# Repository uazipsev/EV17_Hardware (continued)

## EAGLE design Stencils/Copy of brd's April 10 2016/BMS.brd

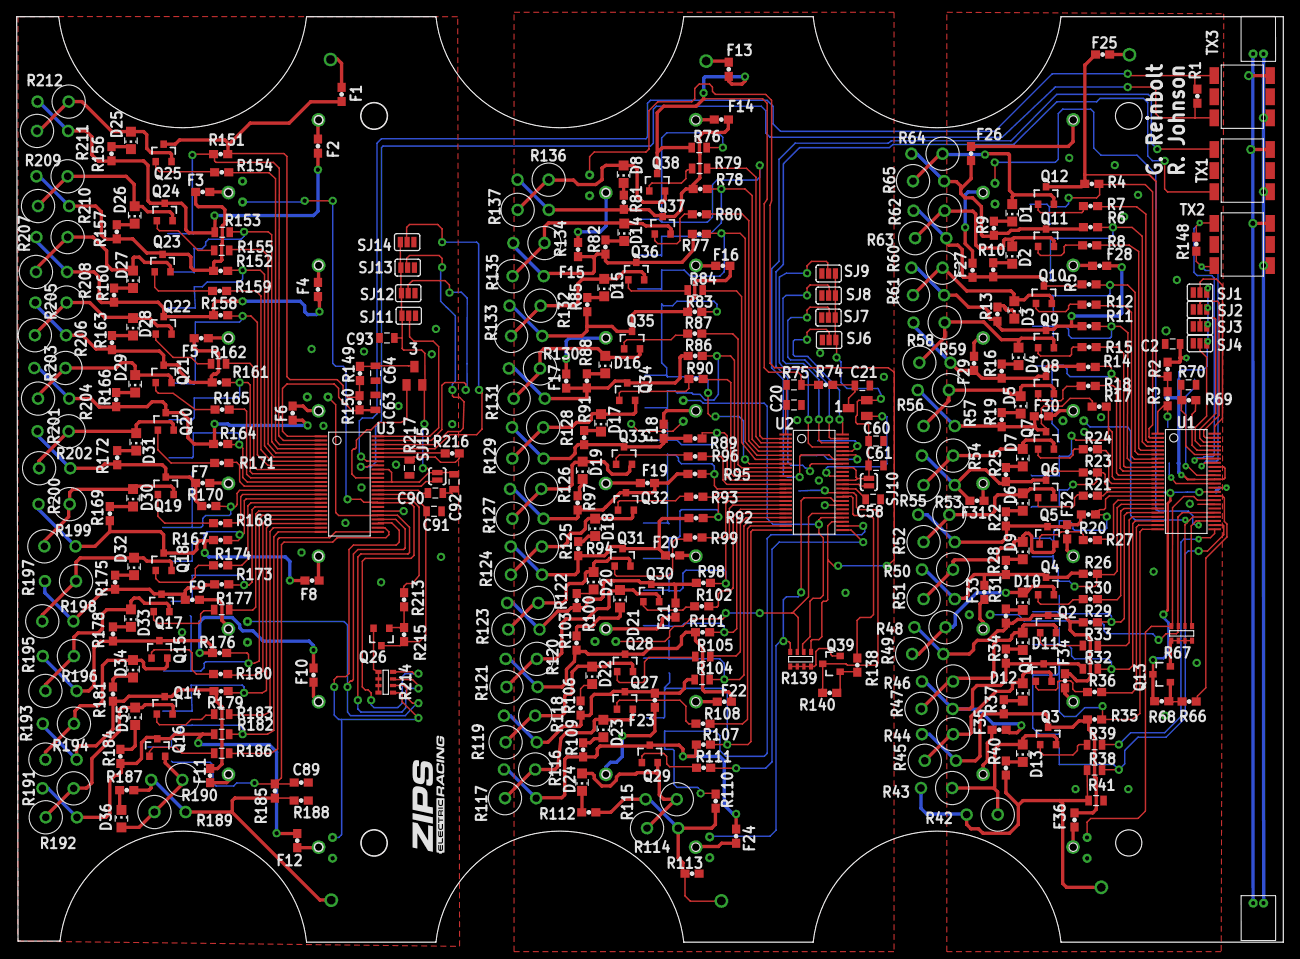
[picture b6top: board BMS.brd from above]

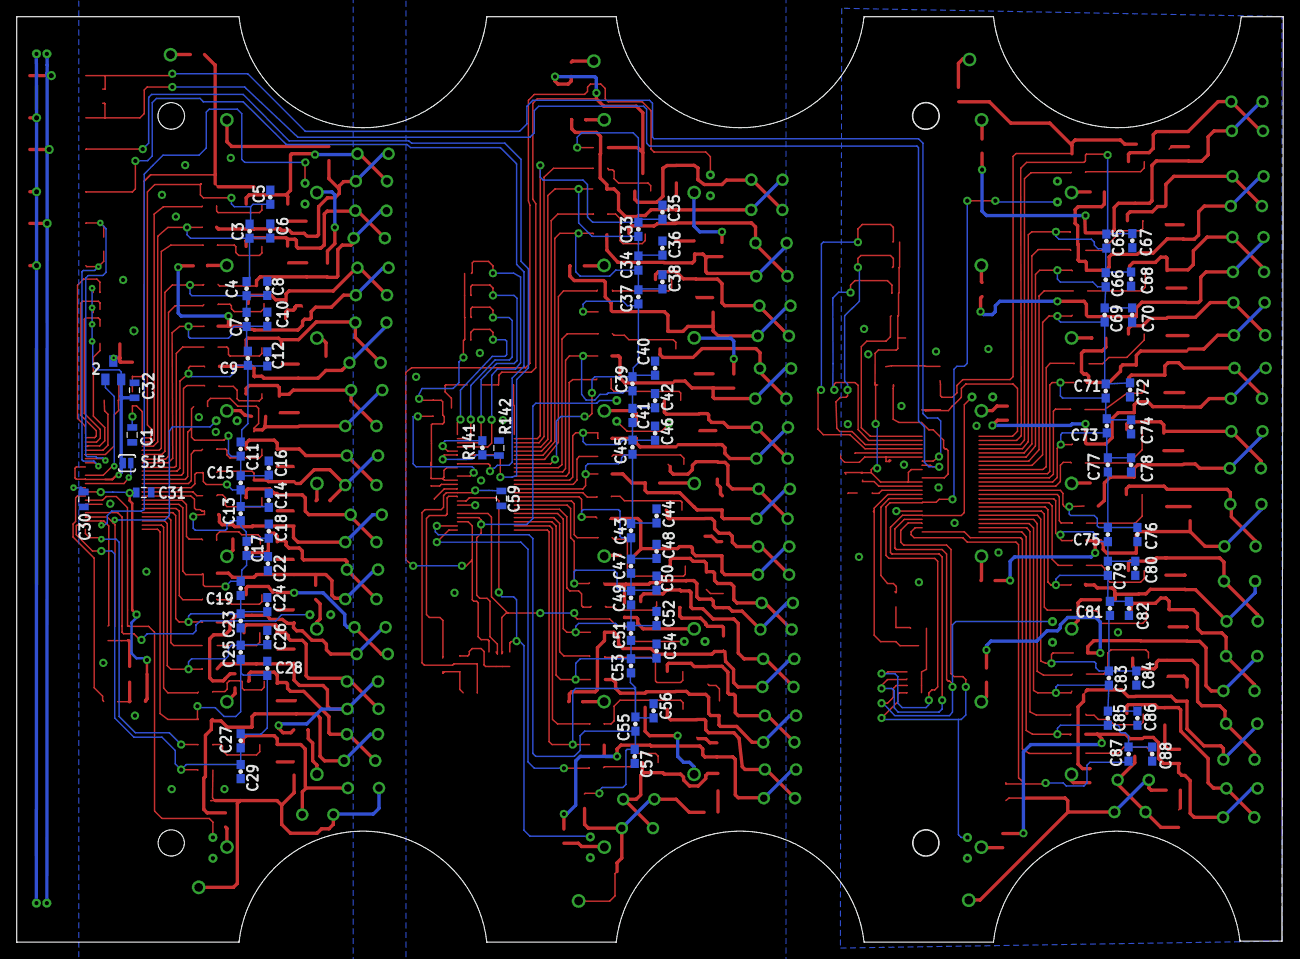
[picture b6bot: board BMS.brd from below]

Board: 2 copper layers, 152.4 x 111.4 mm, 490 parts (83 on the bottom side), 329 nets.

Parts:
1, 2, 3: BCV71SMD; SOT23-BEC
C1, C2, C20, C21, C63, C64: 0.1UF; 0805
C3, C4, C7, C9, C11, C13, C15, C17, C19, C23, C25, C27, C29, C33, C34, C37, C39, C41, C43, C45, C47, C49, C51, C53, C55, C57, C65, C66, C69, C71, C73, C75, C77, C79, C81, C83, C85, C87, C89: 10NF; 0603
C5, C6, C8, C10, C12, C14, C16, C18, C22, C24, C26, C28, C35, C36, C38, C40, C42, C44, C46, C48, C50, C52, C54, C56, C67, C68, C70, C72, C74, C76, C78, C80, C82, C84, C86, C88: DNP; 0603
C30, C31, C32, C58, C59, C60, C61, C90, C91, C92, C93: 1UF; 0805
D1, D2, D3, D4, D5, D6, D7, D8, D9, D10, D11, D12, D13, D14, D15, D16, D17, D18, D19, D20, D21, D22, D23, D24, D25, D26, D27, D28, D29, D30, D31, D32, D33, D34, D35, D36: LED_RED; CHIP_LED0805
F1, F2, F3, F4, F5, F6, F7, F8, F9, F10, F11, F12, F13, F14, F15, F16, F17, F18, F19, F20, F21, F22, F23, F24, F25, F26, F27, F28, F29, F30, F31, F32, F33, F34, F35, F36: FUSE_750MA_63V_0603; 0603
J1, J2: M2_DF13-2P; DF13-2P
Q1, Q2, Q3, Q4, Q5, Q6, Q7, Q8, Q9, Q10, Q11, Q12, Q13, Q14, Q15, Q16, Q17, Q18, Q19, Q20, Q21, Q22, Q23, Q24, Q25, Q26, Q27, Q28, Q29, Q30, Q31, Q32, Q33, Q34, Q35, Q36, Q37, Q38, Q39: BSS308PE; SOT23
R1, R148: DNP; 0603
R2, R3, R4, R5, R6, R11, R14, R17, R20, R23, R26, R29, R35, R74, R77, R78, R83, R86, R89, R92, R95, R98, R101, R107, R110, R149, R150, R151, R152, R158, R161, R164, R167, R170, R173, R176, R179, R185: 100; 0603
R7, R8, R12, R15, R18, R21, R24, R27, R30, R36, R80, R87, R90, R93, R96, R99, R102, R108, R111, R154, R159, R165, R168, R171, R174, R180: 3.3K; 0603
R9, R10, R13, R16, R19, R22, R25, R28, R31, R34, R37, R40, R81, R82, R85, R88, R91, R94, R97, R100, R103, R106, R109, R112, R156, R157, R160, R163, R166, R169, R172, R175, R178, R181, R184, R187: 475; 0603
R32, R38, R75, R76, R104, R153, R182: 100; 0805
R33, R39, R79, R84, R105, R155, R162, R177, R183, R186: 3.3K; 0805
R41: 0; 0805
R42, R43, R44, R45, R46, R47, R48, R49, R50, R51, R52, R53, R54, R55, R56, R57, R58, R59, R60, R61, R62, R63, R64, R65, R114, R115, R116, R117, R118, R119, R120, R121, R122, R123, R124, R125, R126, R127, R128, R129, R130, R131, R132, R133, R134, R135, R136, R137, R189, R190, R191, R192, R193, R194, R195, R196, R197, R198, R199, R200, R201, R202, R203, R204, R205, R206, R207, R208, R209, R210, R211, R212: 16; RR02J16RTB
R66, R138, R213: 1K; 0603
R67, R139, R214: 10K; MNR14
R68, R140, R215: 100K; 0603
R69, R141, R216: 1.2K; 0603
R70, R142, R217: 787; 0805
R71, R72, R73, R143, R144, R145, R146, R147, R218, R219, R220, R221: 10K-NTC; NTC-NXRT15XH103FA5B
R113, R188: 0; 0603
SJ1, SJ2, SJ3, SJ4, SJ6, SJ7, SJ8, SJ9, SJ11, SJ12, SJ13, SJ14: PAD-JUMPER-3-NO_YES_SILK
SJ5, SJ10, SJ15: PAD-JUMPER-2-NO_YES_SILK
TX1, TX2, TX3: PE-68386NLT
U1, U2, U3: LTC6804-2; SSOP-48
U$1, U$2, U$3, U$4, U$5, U$6, U$7, U$8, U$9, U$10, U$11, U$12, U$13, U$14, U$15, U$16, U$17, U$18, U$19, U$20, U$21, U$22, U$23, U$24, U$25, U$26, U$40, U$41, U$42, U$43, U$44, U$45, U$46, U$47, U$48, U$49, U$50, U$51, U$52: POGOPIN
U$27: LOGO16-2-L; 2016-2-LOGO-L

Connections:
A0: SJ9.2, U2.45
A1: SJ8.2, U2.46
A2: SJ7.2, U2.47
A3: SJ6.2, U2.48
A4: SJ4.2, U1.45
A5: SJ3.2, U1.46
A6: SJ2.2, U1.47
A7: SJ1.2, U1.48
A8: SJ14.2, U3.45
A9: SJ13.2, U3.46
A10: SJ12.2, U3.47
A11: SJ11.2, U3.48
C0: C55.2, C57.1, R110.2, U2.26
C1: C53.2, C55.1, C56.1, R107.2, U2.24
C2: C51.2, C53.1, C54.1, R104.2, U2.22
C3: C49.2, C51.1, C52.1, R101.2, U2.20
C4: C47.2, C49.1, C50.1, R98.2, U2.18
C5: C43.2, C47.1, C48.1, R92.2, U2.16
C6: C43.1, C44.1, C45.2, R95.2, U2.14
C7: C41.2, C45.1, C46.1, R89.2, U2.12
C8: C39.2, C41.1, C42.1, R86.2, U2.10
C9: C37.2, C39.1, C40.1, R83.2, U2.8
C10: C34.2, C37.1, C38.1, R77.2, U2.6
C11: C33.2, C34.1, C36.1, R78.2, U2.4
C12: C33.1, C35.1, R76.2, U2.2
C13: C3.1, C5.1, R4.2, U1.2
C14: C3.2, C4.1, C6.1, R6.2, U1.4
C15: C7.2, C9.1, C10.1, R11.2, U1.8
C16: C11.2, C15.1, C16.1, R17.2, U1.12
C17: C13.1, C14.1, C15.2, R23.2, U1.14
C18: C13.2, C17.1, C18.1, R20.2, U1.16
C19: C19.2, C23.1, C24.1, R29.2, U1.20
C20: C23.2, C25.1, C26.1, R32.2, U1.22
C21: C25.2, C27.1, C28.1, R35.2, U1.24
C22: C4.2, C7.1, C8.1, R5.2, U1.6
C23: C27.2, C29.1, R38.2, U1.26
C24: C17.2, C19.1, C22.1, R26.2, U1.18
C25: C9.2, C11.1, C12.1, R14.2, U1.10
C26: C65.1, C67.1, R151.2, U3.2
C27: C65.2, C66.1, C68.1, R153.2, U3.4
C28: C69.2, C71.1, C72.1, R158.2, U3.8
C29: C73.2, C77.1, C78.1, R164.2, U3.12
C30: C75.1, C76.1, C77.2, R170.2, U3.14
C31: C75.2, C79.1, C80.1, R167.2, U3.16
C32: C81.2, C83.1, C84.1, R176.2, U3.20
C33: C83.2, C85.1, C86.1, R179.2, U3.22
C34: C85.2, C87.1, C88.1, R182.2, U3.24
C35: C66.2, C69.1, C70.1, R152.2, U3.6
C36: C87.2, C89.1, R185.2, U3.26
C37: C79.2, C81.1, C82.1, R173.2, U3.18
C38: C71.2, C73.1, C74.1, R161.2, U3.10
DRIVE: 1.B, U2.38
DRIVE1: 2.B, U1.38
DRIVE2: 3.B, U3.38
GND: C63.2, C64.2, C67.2, C68.2, C70.2, C72.2, C74.2, C76.2, C78.2, C80.2, C82.2, C84.2, C86.2, C88.2, C89.2, C90.2, C91.2, C92.2, C93.2, R188.2, R217.1, R218.P$1, R219.P$1, R220.P$1, R221.P$1, SJ11.3, SJ12.3, SJ13.3, SJ14.3, U3.30, U3.31
GNDA: C20.2, C21.2, C35.2, C36.2, C38.2, C40.2, C42.2, C44.2, C46.2, C48.2, C50.2, C52.2, C54.2, C56.2, C57.2, C58.2, C59.2, C60.2, C61.2, R113.2, R142.1, R143.P$1, R144.P$1, R145.P$1, R146.P$1, SJ6.3, SJ7.3, SJ8.3, SJ9.3, U2.30, U2.31
GNDI: C1.2, C2.2, C5.2, C6.2, C8.2, C10.2, C12.2, C14.2, C16.2, C18.2, C22.2, C24.2, C26.2, C28.2, C29.2, C30.2, C31.2, C32.2, R41.2, R70.1, R71.P$1, R72.P$1, R73.P$1, R147.P$1, SJ1.3, SJ2.3, SJ3.3, SJ4.3, U1.30, U1.31
GPIO1: R139.1, R143.P$2, U2.27
GPIO2: R139.2, R144.P$2, U2.28
GPIO3: R139.3, R145.P$2, U2.29
GPIO4: R139.4, R146.P$2, U2.32
GPIO5: R138.2, U2.33
GPIO6: R67.2, R72.P$2, U1.28
GPIO7: R67.1, R71.P$2, U1.27
GPIO8: R67.4, R147.P$2, U1.32
GPIO9: R67.3, R73.P$2, U1.29
GPIO10: R66.2, U1.33
GPIO11: R214.2, R219.P$2, U3.28
GPIO12: R214.1, R218.P$2, U3.27
GPIO13: R214.4, R221.P$2, U3.32
GPIO14: R214.3, R220.P$2, U3.29
GPIO15: R213.2, U3.33
IBIAS: R141.2, U2.44
IBIAS1: R69.2, U1.44
IBIAS2: R216.2, U3.44
ICMP: R141.1, R142.2, U2.43
ICMP1: R69.1, R70.2, U1.43
ICMP2: R216.1, R217.2, U3.43
IMA: TX1.3, U2.41
IMA1: R148.2, TX2.3, U1.41
IMA2: R1.2, TX3.3, U3.41
IPA: TX1.1, U2.42
IPA1: R148.1, TX2.1, U1.42
IPA2: R1.1, TX3.1, U3.42
unnamed: Q12.1, R7.1
unnamed: D1.A, Q12.2, R64.P$2, R65.P$2
unnamed: D1.C, R9.2
unnamed: F26.2, Q11.3, R6.1, R9.1, R64.P$1, R65.P$1
unnamed: Q11.1, R8.1
unnamed: D2.A, Q11.2, R62.P$2, R63.P$2
unnamed: D2.C, R10.2
unnamed: F27.2, Q10.3, R5.1, R10.1, R62.P$1, R63.P$1
unnamed: Q10.1, R12.1
unnamed: D3.A, Q10.2, R60.P$2, R61.P$2
unnamed: D3.C, R13.2
unnamed: F28.2, Q9.3, R11.1, R13.1, R60.P$1, R61.P$1
unnamed: Q9.1, R15.1
unnamed: D4.A, Q9.2, R58.P$2, R59.P$2
unnamed: D4.C, R16.2
unnamed: F29.2, Q8.3, R14.1, R16.1, R58.P$1, R59.P$1
unnamed: Q8.1, R18.1
unnamed: D5.A, Q8.2, R56.P$2, R57.P$2
unnamed: D5.C, R19.2
unnamed: Q6.1, R21.1
unnamed: D6.A, Q6.2, R52.P$2, R53.P$2
unnamed: D6.C, R22.2
unnamed: F30.2, Q7.3, R17.1, R19.1, R56.P$1, R57.P$1
unnamed: Q7.1, R24.1
unnamed: D7.A, Q7.2, R54.P$2, R55.P$2
unnamed: D7.C, R25.2
unnamed: F31.2, Q6.3, R23.1, R25.1, R54.P$1, R55.P$1
unnamed: F32.2, Q5.3, R20.1, R22.1, R52.P$1, R53.P$1
unnamed: Q5.1, R27.1
unnamed: D9.A, Q5.2, R50.P$2, R51.P$2
unnamed: D9.C, R28.2
unnamed: F33.2, Q4.3, R26.1, R28.1, R50.P$1, R51.P$1
unnamed: Q4.1, R30.1
unnamed: D10.A, Q4.2, R48.P$2, R49.P$2
unnamed: D10.C, R31.2
unnamed: F34.2, Q2.3, R29.1, R31.1, R48.P$1, R49.P$1
unnamed: Q2.1, R33.1
unnamed: D11.A, Q2.2, R46.P$2, R47.P$2
unnamed: D11.C, R34.2
unnamed: F35.2, Q1.3, R32.1, R34.1, R46.P$1, R47.P$1
unnamed: Q1.1, R36.1
unnamed: D12.A, Q1.2, R44.P$2, R45.P$2
unnamed: D12.C, R37.2
unnamed: Q3.1, R39.1
unnamed: D13.C, R40.2
unnamed: F25.2, Q12.3, R2.1, R3.1, R4.1
unnamed: D13.A, Q3.2, R42.P$2, R43.P$2
unnamed: R38.1, R40.1, R41.1, R42.P$1, R43.P$1, U$1.1
unnamed: F36.2, Q3.3, R35.1, R37.1, R44.P$1, R45.P$1
unnamed: 2.C, C2.1, R2.2
unnamed: Q13.2, R67.5, R67.6, R67.7, R67.8
unnamed: Q13.1, R66.1, R68.1
unnamed: Q25.1, R154.1
unnamed: D25.A, Q25.2, R211.P$2, R212.P$2
unnamed: D25.C, R156.2
unnamed: F2.2, Q24.3, R153.1, R156.1, R211.P$1, R212.P$1
unnamed: Q24.1, R155.1
unnamed: D26.A, Q24.2, R209.P$2, R210.P$2
unnamed: D26.C, R157.2
unnamed: F3.2, Q23.3, R152.1, R157.1, R209.P$1, R210.P$1
unnamed: Q23.1, R159.1
unnamed: D27.A, Q23.2, R207.P$2, R208.P$2
unnamed: D27.C, R160.2
unnamed: F4.2, Q22.3, R158.1, R160.1, R207.P$1, R208.P$1
unnamed: Q22.1, R162.1
unnamed: D28.A, Q22.2, R205.P$2, R206.P$2
unnamed: D28.C, R163.2
unnamed: F5.2, Q21.3, R161.1, R163.1, R205.P$1, R206.P$1
unnamed: Q21.1, R165.1
unnamed: D29.A, Q21.2, R203.P$2, R204.P$2
unnamed: D29.C, R166.2
unnamed: Q19.1, R168.1
unnamed: D30.A, Q19.2, R199.P$2, R200.P$2
unnamed: D30.C, R169.2
unnamed: F6.2, Q20.3, R164.1, R166.1, R203.P$1, R204.P$1
unnamed: Q20.1, R171.1
unnamed: D31.A, Q20.2, R201.P$2, R202.P$2
unnamed: D31.C, R172.2
unnamed: F7.2, Q19.3, R170.1, R172.1, R201.P$1, R202.P$1
unnamed: F8.2, Q18.3, R167.1, R169.1, R199.P$1, R200.P$1
unnamed: Q18.1, R174.1
unnamed: D32.A, Q18.2, R197.P$2, R198.P$2
unnamed: D32.C, R175.2
unnamed: F9.2, Q17.3, R173.1, R175.1, R197.P$1, R198.P$1
unnamed: Q17.1, R177.1
unnamed: D33.A, Q17.2, R195.P$2, R196.P$2
unnamed: D33.C, R178.2
unnamed: F10.2, Q15.3, R176.1, R178.1, R195.P$1, R196.P$1
unnamed: Q15.1, R180.1
unnamed: D34.A, Q15.2, R193.P$2, R194.P$2
unnamed: D34.C, R181.2
unnamed: F11.2, Q14.3, R179.1, R181.1, R193.P$1, R194.P$1
unnamed: Q14.1, R183.1
unnamed: D35.A, Q14.2, R191.P$2, R192.P$2
unnamed: D35.C, R184.2
unnamed: Q16.1, R186.1
unnamed: D36.C, R187.2
unnamed: F1.2, Q25.3, R149.1, R150.1, R151.1
unnamed: D36.A, Q16.2, R189.P$2, R190.P$2
unnamed: Q38.1, R79.1
unnamed: D8.A, Q38.2, R136.P$2, R137.P$2
unnamed: D8.C, R81.2
unnamed: R185.1, R187.1, R188.1, R189.P$1, R190.P$1, U$14.1
unnamed: F12.2, Q16.3, R182.1, R184.1, R191.P$1, R192.P$1
unnamed: 3.C, C64.1, R149.2
unnamed: F14.2, Q37.3, R78.1, R81.1, R136.P$1, R137.P$1
unnamed: Q37.1, R80.1
unnamed: D14.A, Q37.2, R134.P$2, R135.P$2
unnamed: D14.C, R82.2
unnamed: F15.2, Q36.3, R77.1, R82.1, R134.P$1, R135.P$1
unnamed: Q26.2, R214.5, R214.6, R214.7, R214.8
unnamed: Q36.1, R84.1
unnamed: D15.A, Q36.2, R132.P$2, R133.P$2
unnamed: D15.C, R85.2
unnamed: F16.2, Q35.3, R83.1, R85.1, R132.P$1, R133.P$1
unnamed: Q26.1, R213.1, R215.1
unnamed: Q35.1, R87.1
unnamed: D16.A, Q35.2, R130.P$2, R131.P$2
unnamed: D16.C, R88.2
unnamed: F17.2, Q34.3, R86.1, R88.1, R130.P$1, R131.P$1
unnamed: J1.2, J2.1, TX1.6, TX2.6, TX3.6
unnamed: Q34.1, R90.1
unnamed: D17.A, Q34.2, R128.P$2, R129.P$2
unnamed: D17.C, R91.2
unnamed: J1.1, J2.2, TX1.4, TX2.4, TX3.4
unnamed: Q32.1, R93.1
unnamed: D18.A, Q32.2, R124.P$2, R125.P$2
unnamed: D18.C, R94.2
unnamed: C90.1, U3.35
unnamed: F18.2, Q33.3, R89.1, R91.1, R128.P$1, R129.P$1
unnamed: C30.1, U1.35
unnamed: Q33.1, R96.1
unnamed: D19.A, Q33.2, R126.P$2, R127.P$2
unnamed: D19.C, R97.2
unnamed: F19.2, Q32.3, R95.1, R97.1, R126.P$1, R127.P$1
unnamed: F20.2, Q31.3, R92.1, R94.1, R124.P$1, R125.P$1
unnamed: Q31.1, R99.1
unnamed: D20.A, Q31.2, R122.P$2, R123.P$2
unnamed: D20.C, R100.2
unnamed: F21.2, Q30.3, R98.1, R100.1, R122.P$1, R123.P$1
unnamed: Q30.1, R102.1
unnamed: D21.A, Q30.2, R120.P$2, R121.P$2
unnamed: D21.C, R103.2
unnamed: F22.2, Q28.3, R101.1, R103.1, R120.P$1, R121.P$1
unnamed: Q28.1, R105.1
unnamed: D22.A, Q28.2, R118.P$2, R119.P$2
unnamed: D22.C, R106.2
unnamed: F23.2, Q27.3, R104.1, R106.1, R118.P$1, R119.P$1
unnamed: Q27.1, R108.1
unnamed: D23.A, Q27.2, R116.P$2, R117.P$2
unnamed: D23.C, R109.2
unnamed: Q29.1, R111.1
unnamed: D24.C, R112.2
unnamed: F13.2, Q38.3, R74.1, R75.1, R76.1
unnamed: D24.A, Q29.2, R114.P$2, R115.P$2
unnamed: R110.1, R112.1, R113.1, R114.P$1, R115.P$1, U$40.1
unnamed: F24.2, Q29.3, R107.1, R109.1, R116.P$1, R117.P$1
unnamed: 1.C, C21.1, R74.2
unnamed: Q39.2, R139.5, R139.6, R139.7, R139.8
unnamed: Q39.1, R138.1, R140.1
unnamed: F12.1, U$15.1
unnamed: F11.1, U$16.1
unnamed: F10.1, U$17.1
unnamed: F9.1, U$18.1
unnamed: F8.1, U$19.1
unnamed: F7.1, U$20.1
unnamed: F6.1, U$21.1
unnamed: F5.1, U$22.1
unnamed: F4.1, U$23.1
unnamed: F3.1, U$24.1
unnamed: F2.1, U$25.1
unnamed: F1.1, U$26.1
unnamed: F24.1, U$41.1
unnamed: F23.1, U$42.1
unnamed: F22.1, U$43.1
unnamed: F21.1, U$44.1
unnamed: F20.1, U$45.1
unnamed: F19.1, U$46.1
unnamed: F18.1, U$47.1
unnamed: F17.1, U$48.1
unnamed: F16.1, U$49.1
unnamed: F15.1, U$50.1
unnamed: F14.1, U$51.1
unnamed: F13.1, U$52.1
unnamed: F36.1, U$2.1
unnamed: F35.1, U$3.1
unnamed: F34.1, U$4.1
unnamed: F33.1, U$5.1
unnamed: F32.1, U$6.1
unnamed: F31.1, U$7.1
unnamed: F30.1, U$8.1
unnamed: F29.1, U$9.1
unnamed: F28.1, U$10.1
unnamed: F27.1, U$11.1
unnamed: F26.1, U$12.1
unnamed: F25.1, U$13.1
S1: R111.2, U2.25
S2: R108.2, U2.23
S3: R105.2, U2.21
S4: R102.2, U2.19
S5: R99.2, U2.17
S6: R93.2, U2.15
S7: R96.2, U2.13
S8: R90.2, U2.11
S9: R87.2, U2.9
S10: R84.2, U2.7
S11: R80.2, U2.5
S12: R79.2, U2.3
S13: R7.2, U1.3
S14: R8.2, U1.5
S15: R12.2, U1.7
S16: R15.2, U1.9
S17: R18.2, U1.11
S18: R21.2, U1.15
S19: R24.2, U1.13
S20: R27.2, U1.17
S21: R30.2, U1.19
S22: R33.2, U1.21
S23: R36.2, U1.23
S24: R39.2, U1.25
S25: R154.2, U3.3
S26: R155.2, U3.5
S27: R159.2, U3.7
S28: R162.2, U3.9
S29: R165.2, U3.11
S30: R168.2, U3.15
S31: R171.2, U3.13
S32: R174.2, U3.17
S33: R177.2, U3.19
S34: R180.2, U3.21
S35: R183.2, U3.23
S36: R186.2, U3.25
SWTEN: SJ10.1, U2.36
SWTEN1: SJ5.1, U1.36
SWTEN2: SJ15.1, U3.36
V+: C20.1, R75.2, U2.1
V+1: C1.1, R3.2, U1.1
V+2: C63.1, R150.2, U3.1
VREF1: C58.1, U2.35
VREF2: C59.1, Q39.3, R140.2, U2.34
VREF4: C31.1, Q13.3, R68.2, U1.34
VREF6: C91.1, Q26.3, R215.2, U3.34
VREG: 1.E, C60.1, C61.1, SJ6.1, SJ7.1, SJ8.1, SJ9.1, SJ10.2, U2.37, U2.40
VREG1: 2.E, C32.1, SJ1.1, SJ2.1, SJ3.1, SJ4.1, SJ5.2, U1.37, U1.40
VREG2: 3.E, C92.1, C93.1, SJ11.1, SJ12.1, SJ13.1, SJ14.1, SJ15.2, U3.37, U3.40

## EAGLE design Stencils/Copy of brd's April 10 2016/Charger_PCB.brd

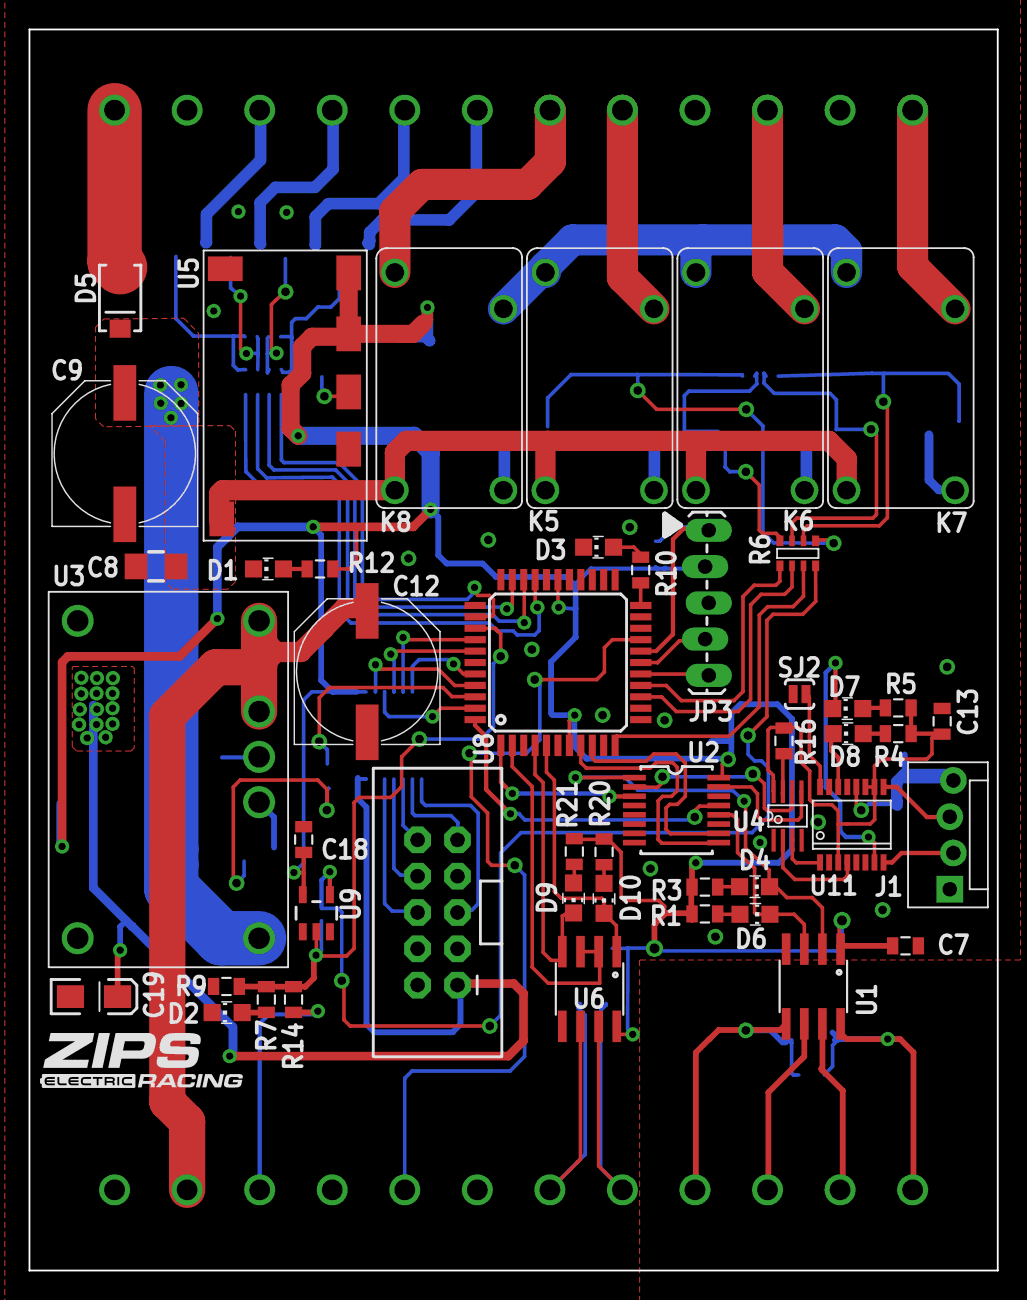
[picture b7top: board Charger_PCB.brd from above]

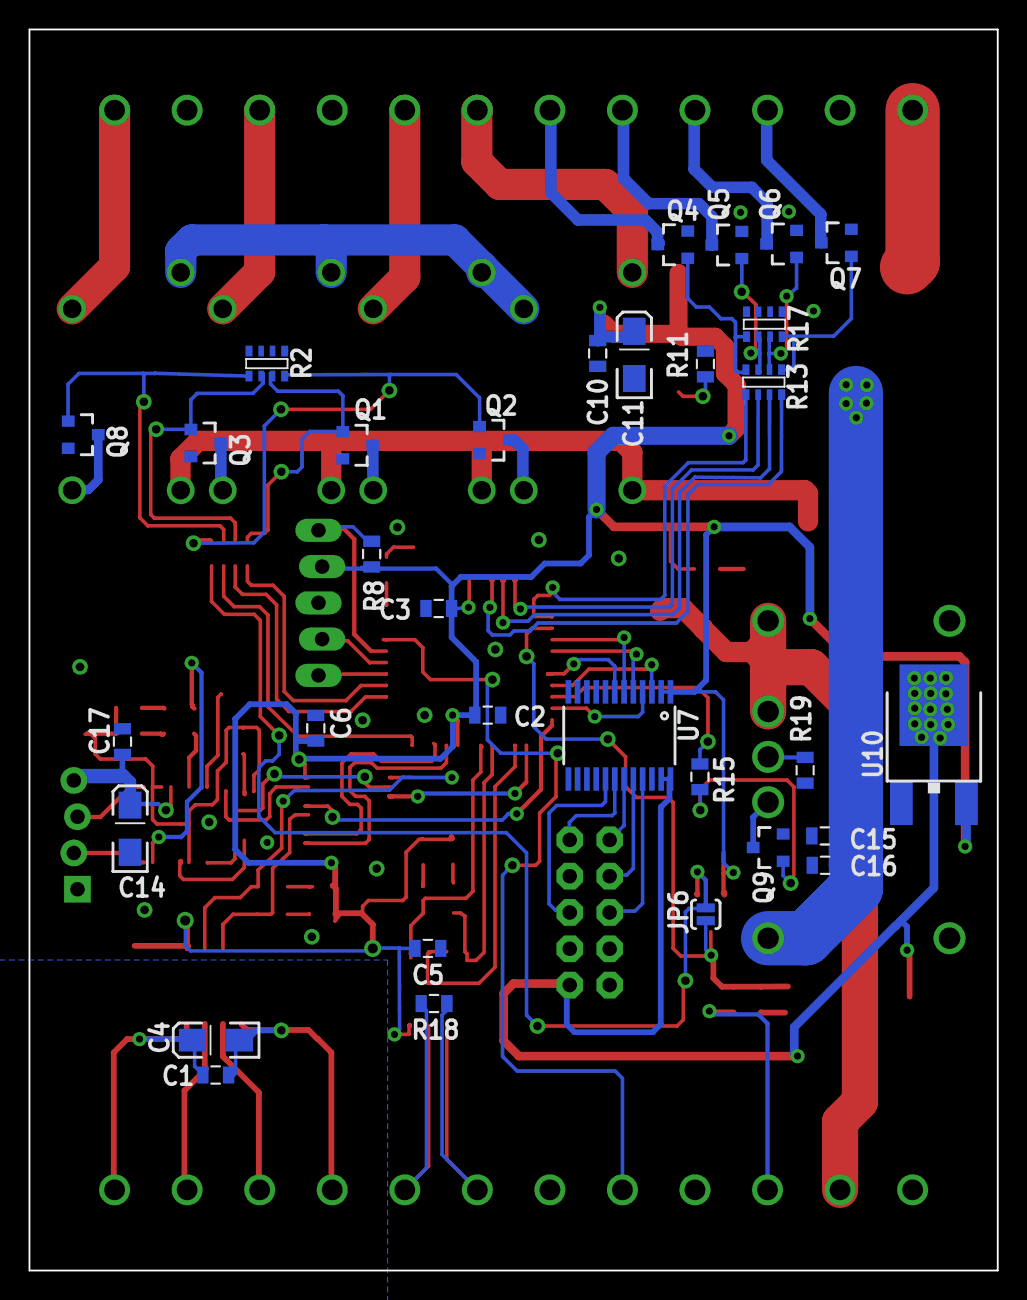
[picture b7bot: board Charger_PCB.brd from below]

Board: 2 copper layers, 67.8 x 86.9 mm, 81 parts (32 on the bottom side), 93 nets.

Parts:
C1, C2, C3, C5, C6, C7, C10, C13, C17, C18: 0.1UF; 0805
C4, C11, C14, C19: 10UF; EIA3216-16V
C8: 1UF; 1206
C9, C12: 100UF; PANASONIC-G
C15, C16: 1UF; 0805
CASE1: DMB-4772-A
D1, D2, D6, D7, D8, D9: GREEN; CHIP_LED0805
D3: AMBER; CHIP_LED0805
D4, D10: RED; CHIP_LED0805
D5: RF201L2STE25; SMA
J1: M4_1X4_LOCK; MOLEX_1X4
J2: M2X5_IDC; 3020-10-0100-00
JP3: 1X05_LOCK_LONGPADS
JP6: SJ_2S-NO
K5, K6, K7, K8: OJ-SS-124LMH2
Q1, Q2, Q3, Q8: NUD3160LT1G; SOT23
Q4, Q5, Q6, Q7, Q9: BSS123; SOT23
R1, R3, R4, R5, R7, R10, R12, R16, R20, R21: 1K; 0805
R2, R17: 10K; MNR14
R6, R13: 1K; MNR14
R8, R9, R14: 10K; 0805
R11: 16.2K; 0805
R15: 1k; 0805
R18: 120; 0805
R19: 383K; 0805
SJ2: PAD-JUMPER-2-NO_YES_SILK
U1: ISO7221; SO-8
U2: CD74HC4052PWR; TSSOP-16
U3: PTN78060HAH
U4: SN74LVC2G241; VFSOP-8
U5: APXW003A0X3-SRZ
U6: SN75HVD08DRSOIC; SO-8
U7: 74LVC8T245; TSSOP-24
U8: PIC18F45K22; TQFP-44
U9: NC7S14M5X; SOT23-5
U10: NCP1117DT_3.3; DPAK
U11: FT230X; SSOP-16
U$1: LOGO16-2-L; 2016-2-LOGO-L

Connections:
3V: C13.1, R4.2, R5.2, R16.2, U4.8, U11.3, U11.10, U11.11
!INH: R15.1, U8.42
+3V3: C19.A, J2.1, U7.23, U7.24, U10.2
+5V: C2.1, C3.1, C5.1, C6.1, C7.1, C10.1, C11.A, C18.1, JP3.2, R1.2, R3.2, R8.2, R12.2, R20.2, R21.2, U1.1, U2.16, U5.5, U5.6, U6.8, U7.1, U7.2, U8.7, U8.28, U9.5, U10.3
+12V: C12.+, CASE1.23, U3.5, U3.6
+24V: C8.1, C9.+, C15.1, C16.1, D5.C, K5.1, K6.1, K7.1, K8.1, U3.2, U5.2
AIR-TOP: R6.2, U8.14
BLUE: R13.6, U8.32
BLUE-HC: CASE1.5, Q5.3
BOTTOM: CASE1.12, K7.C
CS_3V3: J2.10, U7.19
CS_5V: U7.5, U8.38
GND: C2.2, C3.2, C5.2, C6.2, C7.2, C8.2, C9.-, C10.2, C11.C, C12.-, C13.2, C14.C, C15.2, C16.2, C17.2, C18.2, C19.C, CASE1.2, CASE1.9, CASE1.11, CASE1.19, CASE1.21, CASE1.24, D1.C, D2.C, D3.C, J1.1, J2.2, JP3.3, Q1.2, Q2.2, Q3.2, Q4.2, Q5.2, Q6.2, Q7.2, Q8.2, Q9.2, R2.1, R2.2, R2.3, R2.4, R9.1, R11.1, R17.1, R17.2, R17.3, R17.4, R19.1, SJ2.1, U1.4, U2.6, U2.7, U2.8, U3.1, U3.7, U4.1, U4.4, U5.1, U5.3, U6.5, U7.11, U7.12, U7.13, U7.22, U8.6, U8.29, U9.3, U10.1, U11.5, U11.13
GPIO: CASE1.20, U8.19
GREEN: R13.7, U8.31
GREEN-HC: CASE1.4, Q6.3
HORN: R13.8, U8.30
HORN-HC: CASE1.3, Q7.3
IMD-R-SET: K8.2, Q2.3
IMD-R-SET1: K6.2, Q3.3
IMD-R-SET2: K5.2, Q1.3
IMD-R-SET3: K7.2, Q8.3
IMD_IN: CASE1.22, R14.2
IMD_STAT: JP6.2, R7.2, R9.2, R14.1, U8.36, U9.2
INPUT: CASE1.7, K8.NO
LCD_DC_3V3: J2.6, U7.21
LCD_DC_5V: U7.3, U8.41
LCD_RES_3V3: J2.5, U7.17
LCD_RES_5V: U7.7, U8.40
MAIN: CASE1.10, K6.C
MOSI_3V3: J2.8, U7.20
MOSI_5V: U7.4, U8.43
unnamed: D3.A, R10.1
unnamed: R10.2, U8.22
unnamed: C1.1, C4.A, CASE1.13, U1.8
unnamed: CASE1.14, U1.7
unnamed: CASE1.15, U1.6
unnamed: C1.2, C4.C, CASE1.16, U1.5
unnamed: D6.A, R1.1
unnamed: D4.A, R3.1
unnamed: D7.A, R5.1
unnamed: D8.A, R4.1
unnamed: D2.A, R7.1
unnamed: Q9.3, U3.3
unnamed: K5.NO, K6.NO, K7.NO, K8.C
unnamed: Q2.1, R2.8, R6.5
unnamed: Q8.1, R2.5, R6.6
unnamed: R11.2, U5.4
unnamed: D1.A, R12.1
unnamed: R19.2, U3.4
unnamed: Q9.1, R15.2
unnamed: D9.A, R21.1
unnamed: Q4.1, R13.4, R17.5
unnamed: D10.A, R20.1
unnamed: Q3.1, R2.6, R6.7
unnamed: Q1.1, R2.7, R6.8
unnamed: Q5.1, R13.3, R17.6
unnamed: Q6.1, R13.2, R17.7
unnamed: Q7.1, R13.1, R17.8
unnamed: SJ2.2, U11.16
unnamed: CASE1.1, D5.A
unnamed: JP6.1, R6.4, U9.4
unnamed: D7.C, U11.7
unnamed: D8.C, U11.14
unnamed: U4.2, U11.4
unnamed: JP3.4, U8.17
unnamed: U4.3, U11.1
unnamed: J1.3, U11.9
unnamed: JP3.5, U8.16
unnamed: JP3.1, R8.1, U8.18
unnamed: J1.2, U11.8
unnamed: R16.1, U4.7
unnamed: C14.A, C17.1, J1.4, U11.12
POWER: R6.1, U8.15
PRE&HV-: R6.3, U8.11
PRE-CHARGE: CASE1.8, K5.C
RS-A: CASE1.18, R18.1, U6.6
RS-B: CASE1.17, R18.2, U6.7
RX1: U2.3, U8.1
RX2: D10.C, U6.1, U8.5
RX_POWER: D4.C, U1.2, U2.1
S0: U2.10, U8.9
S1: U2.9, U8.8
SCK_3V3: J2.9, U7.18
SCK_5V: U7.6, U8.37
TX1: U2.13, U8.44
TX2: D9.C, U6.4, U8.4
TX_POWER: D6.C, U1.3, U2.12
U6-RE/DE: U6.2, U6.3, U8.2
USBRX: U2.2, U4.6
USBTX: U2.15, U4.5
YELLOW: R13.5, U8.35
YELLOW-HC: CASE1.6, Q4.3

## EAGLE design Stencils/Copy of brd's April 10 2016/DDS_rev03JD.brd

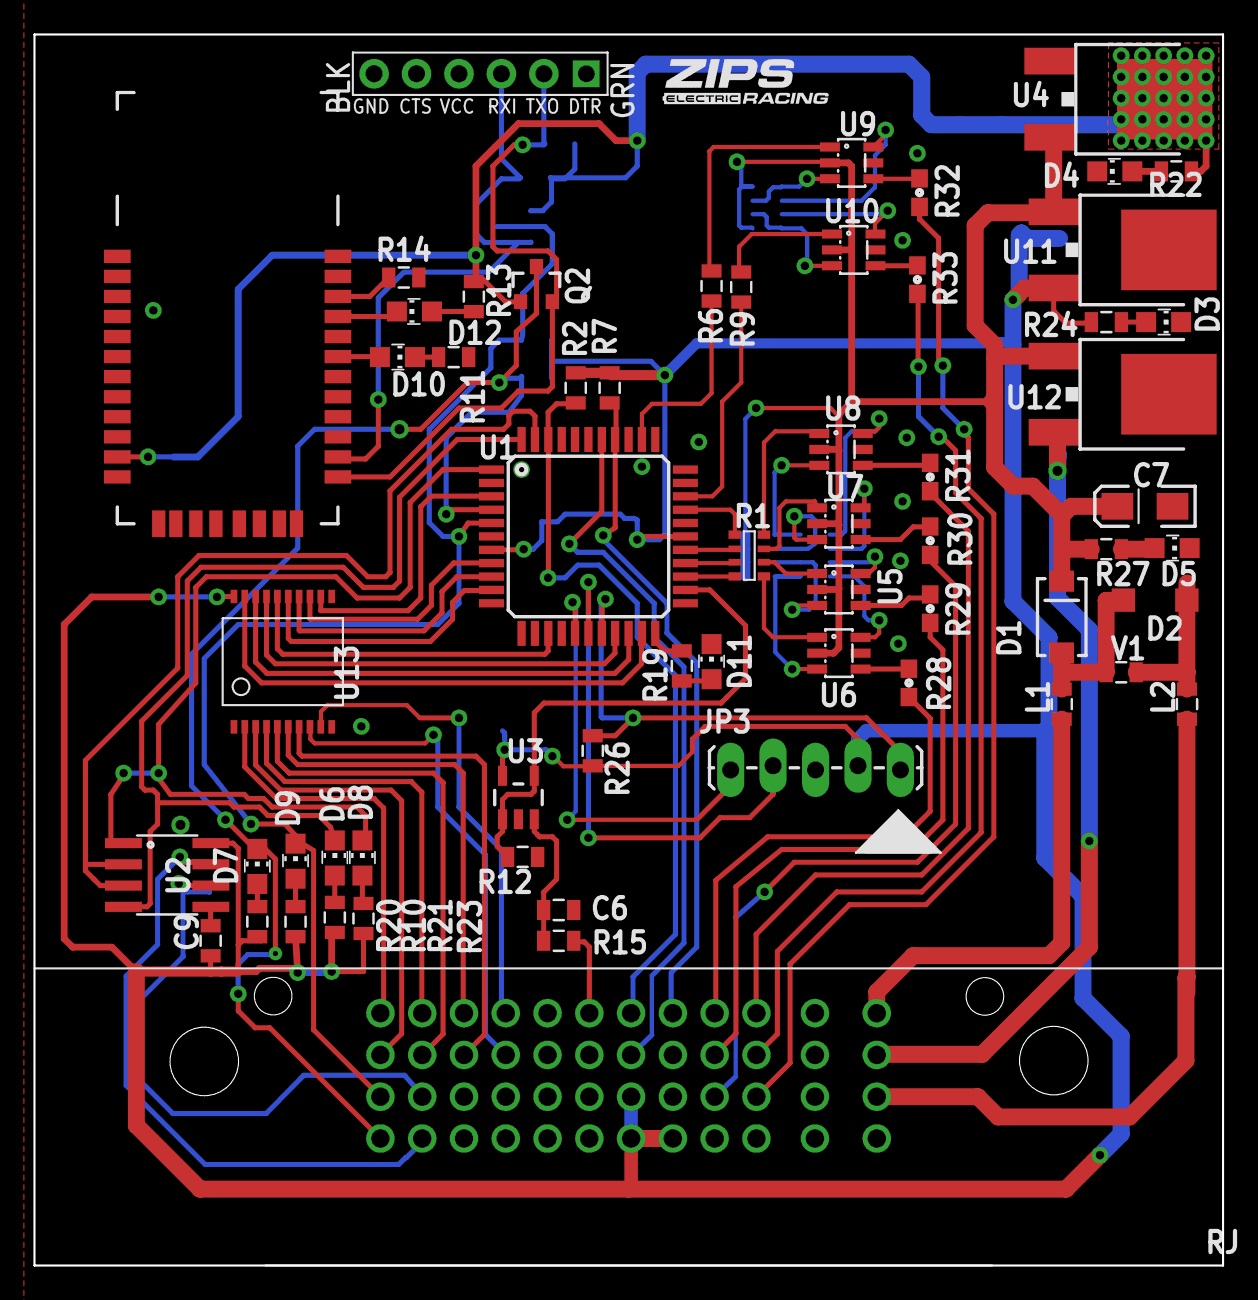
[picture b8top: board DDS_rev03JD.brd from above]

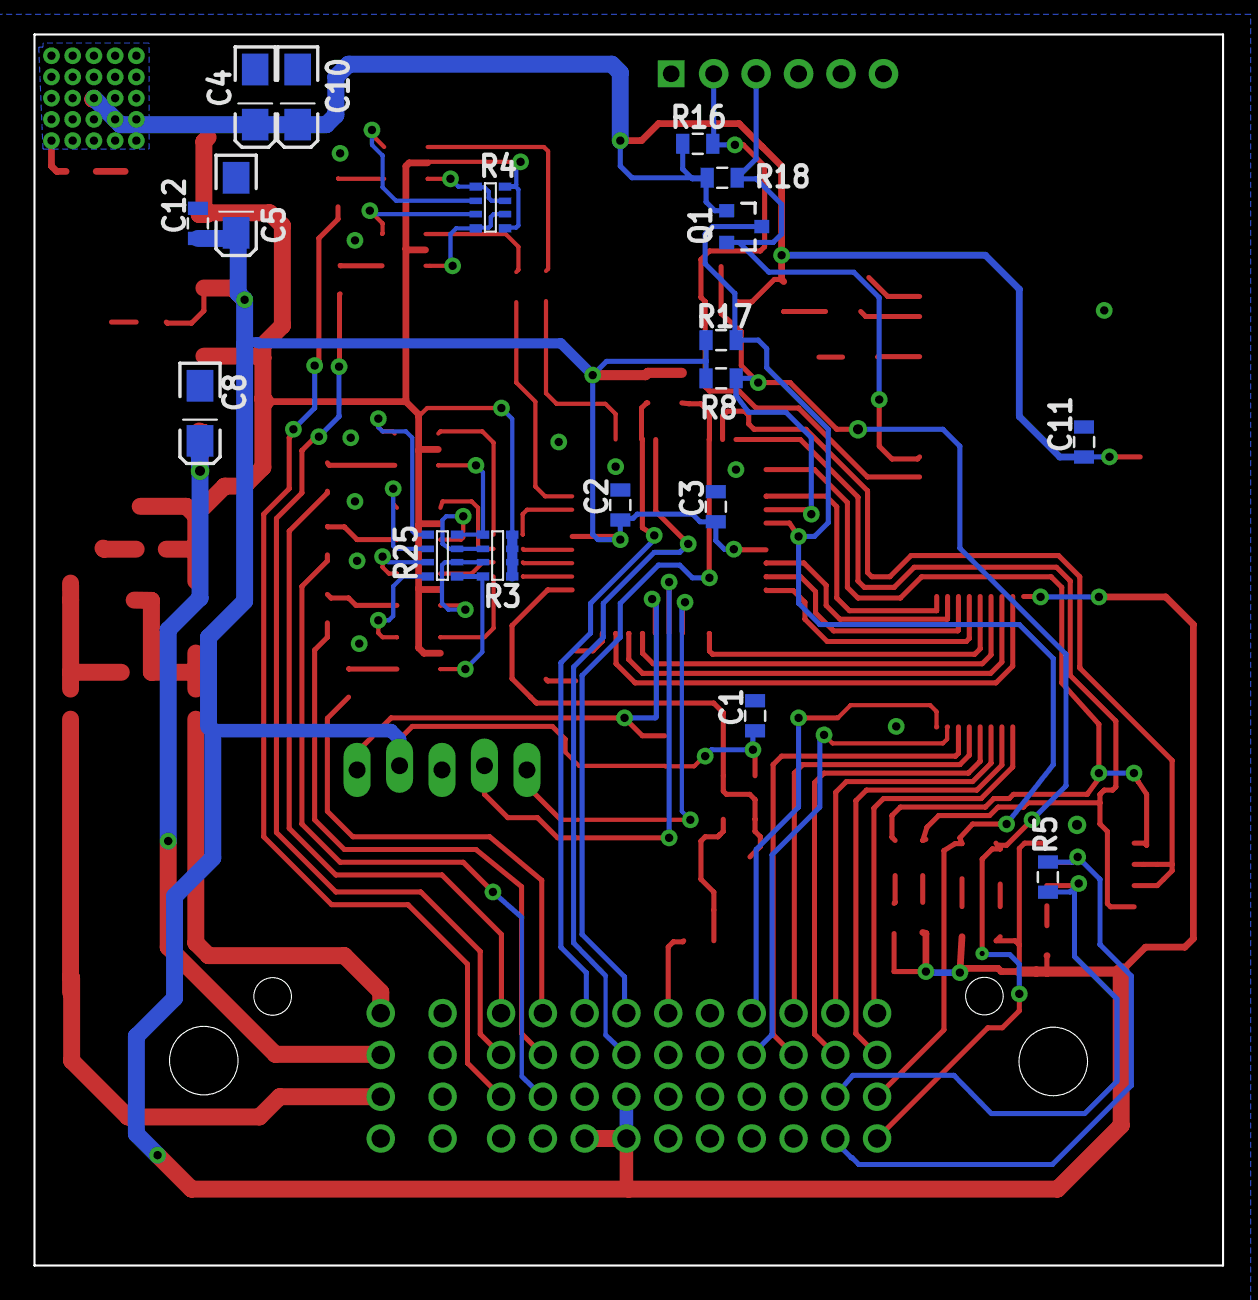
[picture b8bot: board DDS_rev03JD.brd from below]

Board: 2 copper layers, 71.1 x 73.7 mm, 81 parts (18 on the bottom side), 92 nets.

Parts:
C1, C2, C3, C9, C11, C12: \0.1UF; 0805
C4, C5, C7, C8, C10: 10UF; EIA3216-16V
C6: 1UF; 0805
D1: S1B; SMA
D2: 11V; SOD-123
D3, D4, D5, D6, D7: GREEN; CHIP_LED0805
D8, D9: RED; CHIP_LED0805
D10, D11: AMBER; CHIP_LED0805
D12: YELLOW; CHIP_LED0805
J1: 36638NEW; 36638-M
JP3: 1X05_LOCK_LONGPADS
JP19: FTDI_DEVICE; FTDI_DEVICE_SIDE
L1, L2: L_FB_2A; 0805
Q1, Q2: BSS123; SOT23
R1: 1K; MNR14
R2, R7: 2.2K; 0805
R3, R25: RN-4_10K; MNR14
R4: 10K; MNR14
R5: 120; 0805
R6, R9, R10, R19, R20, R21, R23, R24: 1K; 0805
R8, R12, R15, R16, R17, R18, R26: 10K; 0805
R11, R13, R22: 330; 0805
R14: 100K; 0805
R27: 1.2K; 0805
R28, R29, R30, R31, R32, R33: RESPLACEHOLDER; 0603
U1: PIC18F45K22; TQFP-44
U2: SN75HVD08DRSOIC; SO-8
U3: OPA344; SOT23-5
U4: NCP1117DT_3.3; DPAK
U5, U6, U7, U8, U9, U10: DMG6602SVTQ; SOT23-6
U11, U12: NCV7805BDTRKG; DPAK
U13: MAX6818; SSOP-20
U$1: INDPK1; PICKIT-PIN-1
U$2: BLUETOOTH-RN41"; RN41
U$3: LOGO16-2-M; 2016-2-LOGO-M
V1: 10.8V; 0805

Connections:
5V2: C8.A, J1.46, U12.3
+: J1.45, L1.1
+3V3: C4.A, C10.A, C11.1, Q1.1, Q2.1, R13.2, R16.2, R18.2, R22.2, U4.2, U$2.11
+5V: C1.1, C2.1, C3.1, C5.A, C9.1, C12.1, J1.27, J1.28, J1.32, JP3.2, R2.2, R7.2, R8.2, R10.2, R17.2, R20.2, R21.2, R23.2, R24.2, R26.2, U1.7, U1.28, U2.8, U3.5, U11.3, U13.20
+9V: C7.A, D1.C, R3.1, R3.2, R3.3, R3.4, R4.5, R4.8, R27.2, U4.3, U5.2, U6.2, U7.2, U8.2, U9.2, U10.2, U11.1, U12.1
-: J1.47, L2.1
ACK: J1.13, U13.9
B1: J1.1, U13.2
B2: J1.2, U13.3
BREAK: J1.6, U13.5
BSAVE: J1.5, U13.4
GHT: D1.A, D2.C, L1.2, V1.1
GND: C1.2, C2.2, C3.2, C4.C, C5.C, C6.2, C7.C, C8.C, C9.2, C10.C, C11.2, C12.2, D2.A, D3.C, D4.C, D5.C, D11.C, J1.11, J1.12, J1.15, J1.16, J1.17, J1.18, J1.19, J1.20, J1.22, J1.23, J1.24, J1.40, J1.41, J1.42, J1.43, J1.44, J1.48, JP3.3, JP19.P$6, L2.2, R11.1, R12.1, R14.1, U1.6, U1.29, U2.5, U3.2, U4.1, U5.5, U6.5, U7.5, U8.5, U9.5, U10.5, U11.2, U12.2, U13.1, U13.10, U$2.1, U$2.12, U$2.28, U$2.29, V1.2
LED0: R6.1, U1.35
LED1: R9.1, U1.31
LED2: R1.1, U1.30
LED3: R1.2, U1.27
LED4: R1.3, U1.26
LED5: R1.4, U1.25
unnamed: D11.A, R19.1
unnamed: R19.2, U1.22
unnamed: JP19.P$3, Q1.2, R18.1, U$2.14
unnamed: J1.10, U13.7
unnamed: R28.1, U6.4
unnamed: D12.A, R13.1
unnamed: R25.8, U6.6
unnamed: D12.C, U$2.21
unnamed: D10.A, U$2.19
unnamed: R14.2, U$2.22
unnamed: D6.A, R21.1
unnamed: JP19.P$2, Q2.2, R16.1, U$2.13
unnamed: D10.C, R11.2
unnamed: D8.A, R23.1
unnamed: D5.A, R27.1
unnamed: R3.8, R25.1, U6.3
unnamed: D9.A, R10.1
unnamed: D7.A, R20.1
unnamed: D3.A, R24.1
unnamed: R29.1, U5.4
unnamed: R25.7, U5.6
unnamed: R3.7, R25.2, U5.3
unnamed: R1.5, U6.1
unnamed: J1.21, R15.2
unnamed: D4.A, R22.1
unnamed: C6.1, R15.1, U3.3
unnamed: R25.6, U7.6
unnamed: R3.6, R25.3, U7.3
unnamed: R1.6, U5.1
unnamed: R25.5, U8.6
unnamed: R3.5, R25.4, U8.3
unnamed: R30.1, U7.4
unnamed: R4.1, R4.7, U9.3
unnamed: R4.2, U9.6
unnamed: R31.1, U8.4
unnamed: R4.3, U10.6
unnamed: R4.4, R4.6, U10.3
unnamed: R32.1, U9.4
unnamed: R33.1, U10.4
unnamed: JP3.4, U1.17
unnamed: R1.7, U7.1
unnamed: R1.8, U8.1
unnamed: JP3.5, U1.16
unnamed: R6.2, U9.1
unnamed: R9.2, U10.1
unnamed: JP3.1, R26.1, U1.18
O1: U1.3, U13.12
O2: U1.8, U13.13
O3: U1.9, U13.14
O4: U1.10, U13.15
O5: U1.14, U13.16
O6: U1.19, U13.17
O7: U1.20, U13.18
O8: U1.21, U13.19
POS-SWITCH: J1.26, U1.38
RS-A: J1.7, R5.1, U2.6
RS-B: J1.8, R5.2, U2.7
RX1: D8.C, U1.1, U2.1
RX2: D9.C, J1.3, Q1.3, R17.1, U1.5
SCL: J1.29, R7.1, U1.37
SDA: J1.25, R2.1, U1.42
START: J1.9, U13.6
TALK: J1.14, U13.8
TX1: D6.C, U1.44, U2.4
TX2: D7.C, J1.4, Q2.3, R8.1, U1.4
U2-RE/DE: U1.43, U2.2, U2.3
VOL: R12.2, U1.24, U3.1, U3.4
_OLED0: J1.39, R32.2
_OLED1: J1.38, R33.2
_OLED2: J1.37, R31.2
_OLED3: J1.35, R30.2
_OLED4: J1.34, R29.2
_OLED5: J1.33, R28.2
